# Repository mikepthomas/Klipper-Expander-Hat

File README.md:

# Klipper Fan Hat

[Interactive bom](https://klipper-fan-hat.mikethomas.info/)

### A Hat to use with the [Raspberry Pi as a Secondary MCU in Klipper](https://www.klipper3d.org/RPi_microcontroller.html):
- SKR Pico compatible input for powering the Pi and Serial communication
- 5 Mosfet outputs (with 2 pin JST-XH connectors standard on most fans used on 3D printers)
- Voltage selector jumpers to power each fan from either 5V or VCC supplied by screw terminal
- I2C and 1-Wire and SPI headers for connecting accesories to the Raspberry Pi
- 6 headers connected to General Purpose GPIO pins for accesories such as Filament Run Out Sensors
- On Board DS18B20 Temperature Sensor

### Documentation

[Documentation and Setup information here](Documentation/README.md)

 Parts that I sourced for assembly:
- 1206 Capacitor Set [Ali Express](https://www.aliexpress.com/item/1005002907508304.html)
- 1206 LEDs [Ali Express](https://www.aliexpress.com/item/1005003836509392.html)
- 1206 Resistor Set [Ali Express](https://www.aliexpress.com/item/33029877427.html)
- 2510 Axial Fan [Ali Express](https://www.aliexpress.com/item/32807610078.html)
- Blade Fuse Holder [Ali Express](https://www.aliexpress.com/item/1005003194700697.html)
- DIP-8 24C32 EEPROM [Ali Express](https://www.aliexpress.com/item/33036366759.html)
- DIP-8 Socket [Ali Express](https://www.aliexpress.com/item/1005001650813894.html)
- IRLML6344TRPBF Mosfets [Ali Express](https://www.aliexpress.com/item/1005004711783484.html)
- JST-XH Connector Set [Ali Express](https://www.aliexpress.com/item/33000442968.html)
- Jumper Caps [Ali Express](https://www.aliexpress.com/item/1005004482029258.html)
- KF301 Screw Terminal [Ali Express](https://www.aliexpress.com/item/1005003311688833.html)
- M2.5x14 BHCS [Ali Express](https://www.aliexpress.com/item/1005004123548619.html)
- Pin Header Set [Amazon](https://www.amazon.co.uk/gp/product/B07CWSXY7P)
- Raspberry Pi Headers and Spacers [Amazon](https://www.amazon.co.uk/gp/product/B07PHBTTGV)
- DS18B20 Temperature Sensor [Ali Express](https://www.aliexpress.com/item/1783091649.html)

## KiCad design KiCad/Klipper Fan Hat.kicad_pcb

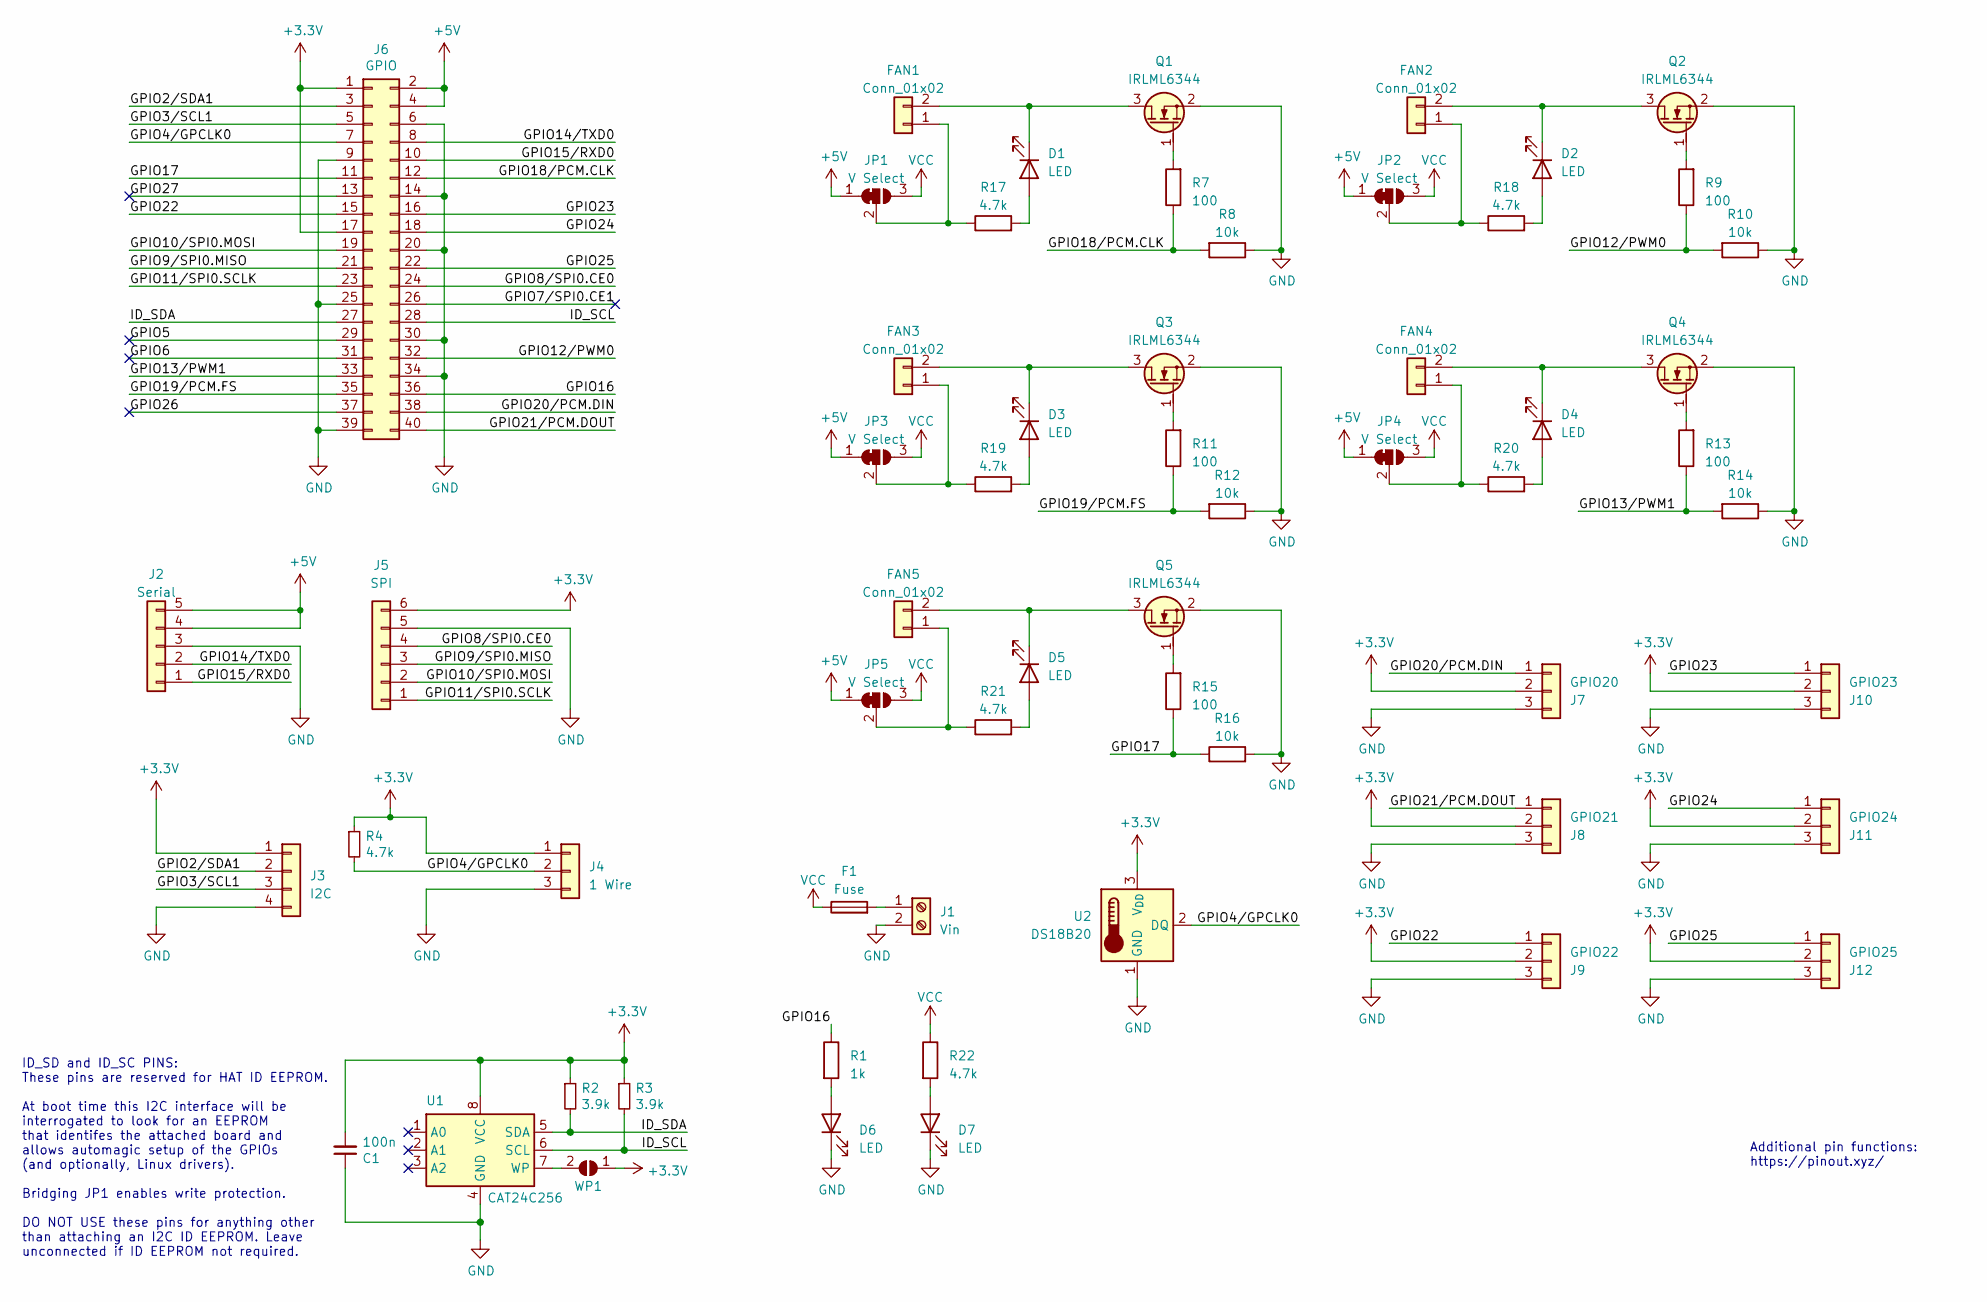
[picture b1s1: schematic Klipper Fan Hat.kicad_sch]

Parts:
C1: 100n; C_1206_3216Metric
D1, D2, D3, D4, D5, D6, D7: LED; LED_1206_3216Metric_ReverseMount_Hole1.8x2.4mm
F1: Fuse; Fuseholder_Blade_Mini_Keystone_3568
FAN1, FAN2, FAN3, FAN4, FAN5: Conn_01x02; JST_XH_B2B-XH-A_1x02_P2.50mm_Vertical
GPIO20: J7; PinHeader_1x03_P2.54mm_Vertical
GPIO21: J8; PinHeader_1x03_P2.54mm_Vertical
GPIO22: J9; PinHeader_1x03_P2.54mm_Vertical
GPIO23: J10; PinHeader_1x03_P2.54mm_Vertical
GPIO24: J11; PinHeader_1x03_P2.54mm_Vertical
GPIO25: J12; PinHeader_1x03_P2.54mm_Vertical
J1: Vin; TerminalBlock_bornier-2_P5.08mm
J2: Serial; JST_XH_B5B-XH-A_1x05_P2.50mm_Vertical
J3: I2C; JST_XH_B4B-XH-A_1x04_P2.50mm_Vertical
J4: 1 Wire; JST_XH_B3B-XH-A_1x03_P2.50mm_Vertical
J5: SPI; PinHeader_1x06_P2.54mm_Vertical
J6: GPIO; PinSocket_2x20_P2.54mm_Vertical
JP1, JP2, JP3, JP4, JP5: V Select; PinHeader_1x03_P2.54mm_Vertical
Q1, Q2, Q3, Q4, Q5: IRLML6344; TSOT-23
R1: 1k; R_1206_3216Metric
R2, R3: 3.9k; R_1206_3216Metric
R4, R17, R18, R19, R20, R21, R22: 4.7k; R_1206_3216Metric
R7, R9, R11, R13, R15: 100; R_1206_3216Metric
R8, R10, R12, R14, R16: 10k; R_1206_3216Metric
U1: CAT24C256; DIP-8_W7.62mm
U2: DS18B20; TO-92_Inline
WP1: ID_WP; PinHeader_1x02_P2.54mm_Vertical

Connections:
+3V3: C1.2, GPIO20.2, GPIO21.2, GPIO22.2, GPIO23.2, GPIO24.2, GPIO25.2, J3.1, J4.1, J5.6, J6.1, J6.17, R2.1, R3.1, R4.1, U1.8 (VCC), U2.3 (V_{DD}), WP1.1 (A)
+5V: J2.4, J2.5, J6.2, J6.4, JP1.1 (A), JP2.1 (A), JP3.1 (A), JP4.1 (A), JP5.1 (A)
/GPIO2/SDA1: J3.2, J6.3
/GPIO3/SCL1: J3.3, J6.5
/GPIO4/GPCLK0: J4.2, J6.7, R4.2, U2.2 (DQ)
/GPIO5: J6.29
/GPIO6: J6.31
/GPIO7/SPI0.CE1: J6.26
/GPIO8/SPI0.CE0: J5.4, J6.24
/GPIO9/SPI0.MISO: J5.3, J6.21
/GPIO10/SPI0.MOSI: J5.2, J6.19
/GPIO11/SPI0.SCLK: J5.1, J6.23
/GPIO12/PWM0: J6.32, R9.1, R10.2
/GPIO13/PWM1: J6.33, R13.1, R14.2
/GPIO14/TXD0: J2.2, J6.8
/GPIO15/RXD0: J2.1, J6.10
/GPIO16: J6.36, R1.1
/GPIO17: J6.11, R15.1, R16.1
/GPIO18/PCM.CLK: J6.12, R7.1, R8.2
/GPIO19/PCM.FS: J6.35, R11.1, R12.2
/GPIO20/PCM.DIN: GPIO20.1, J6.38
/GPIO21/PCM.DOUT: GPIO21.1, J6.40
/GPIO22: GPIO22.1, J6.15
/GPIO23: GPIO23.1, J6.16
/GPIO24: GPIO24.1, J6.18
/GPIO25: GPIO25.1, J6.22
/GPIO26: J6.37
/GPIO27: J6.13
/ID_SCL: J6.28, R3.2, U1.6 (SCL)
/ID_SDA: J6.27, R2.2, U1.5 (SDA)
GND: C1.1, D6.1 (K), D7.1 (K), GPIO20.3, GPIO21.3, GPIO22.3, GPIO23.3, GPIO24.3, GPIO25.3, J1.2, J2.3, J3.4, J4.3, J5.5, J6.6, J6.9, J6.14, J6.20, J6.25, J6.30, J6.34, J6.39, Q1.2 (S), Q2.2 (S), Q3.2 (S), Q4.2 (S), Q5.2 (S), R8.1, R10.1, R12.1, R14.1, R16.2, U1.4 (GND), U2.1 (GND)
unnamed: D1.2 (A), R17.2
unnamed: D1.1 (K), FAN1.2, Q1.3 (D)
unnamed: D2.2 (A), R18.2
unnamed: D2.1 (K), FAN2.2, Q2.3 (D)
unnamed: D3.2 (A), R19.2
unnamed: D3.1 (K), FAN3.2, Q3.3 (D)
unnamed: D4.2 (A), R20.2
unnamed: D4.1 (K), FAN4.2, Q4.3 (D)
unnamed: D5.2 (A), R21.2
unnamed: D5.1 (K), FAN5.2, Q5.3 (D)
unnamed: D6.2 (A), R1.2
unnamed: D7.2 (A), R22.2
unnamed: FAN1.1, JP1.2 (C), R17.1
unnamed: FAN2.1, JP2.2 (C), R18.1
unnamed: FAN3.1, JP3.2 (C), R19.1
unnamed: FAN4.1, JP4.2 (C), R20.1
unnamed: FAN5.1, JP5.2 (C), R21.1
unnamed: F1.2, J1.1
unnamed: Q1.1 (G), R7.2
unnamed: Q2.1 (G), R9.2
unnamed: Q3.1 (G), R11.2
unnamed: Q4.1 (G), R13.2
unnamed: Q5.1 (G), R15.2
unnamed: U1.7 (WP), WP1.2 (B)
VCC: F1.1, JP1.3 (B), JP2.3 (B), JP3.3 (B), JP4.3 (B), JP5.3 (B), R22.1

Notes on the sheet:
Additional pin functions: https://pinout.xyz/
ID_SD and ID_SC PINS: These pins are reserved for HAT ID EEPROM. At boot time this I2C interface will be interrogated to look for an EEPROM that identifes the attached board and allows automagic setup of the GPIOs (and optionally, Linux drivers). Bridging JP1 enables write protection. DO NOT USE th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

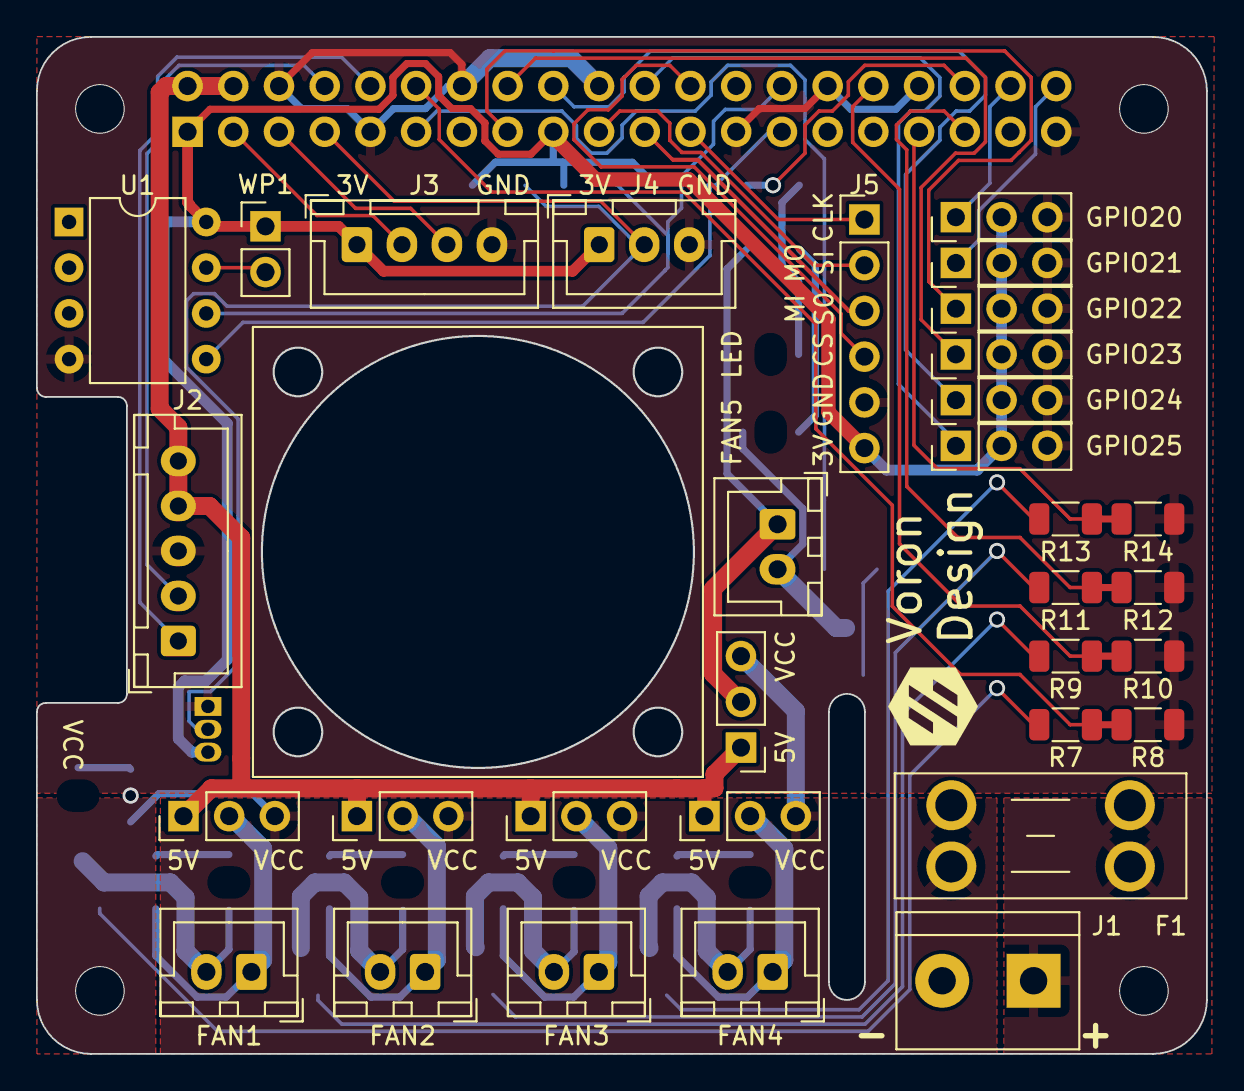
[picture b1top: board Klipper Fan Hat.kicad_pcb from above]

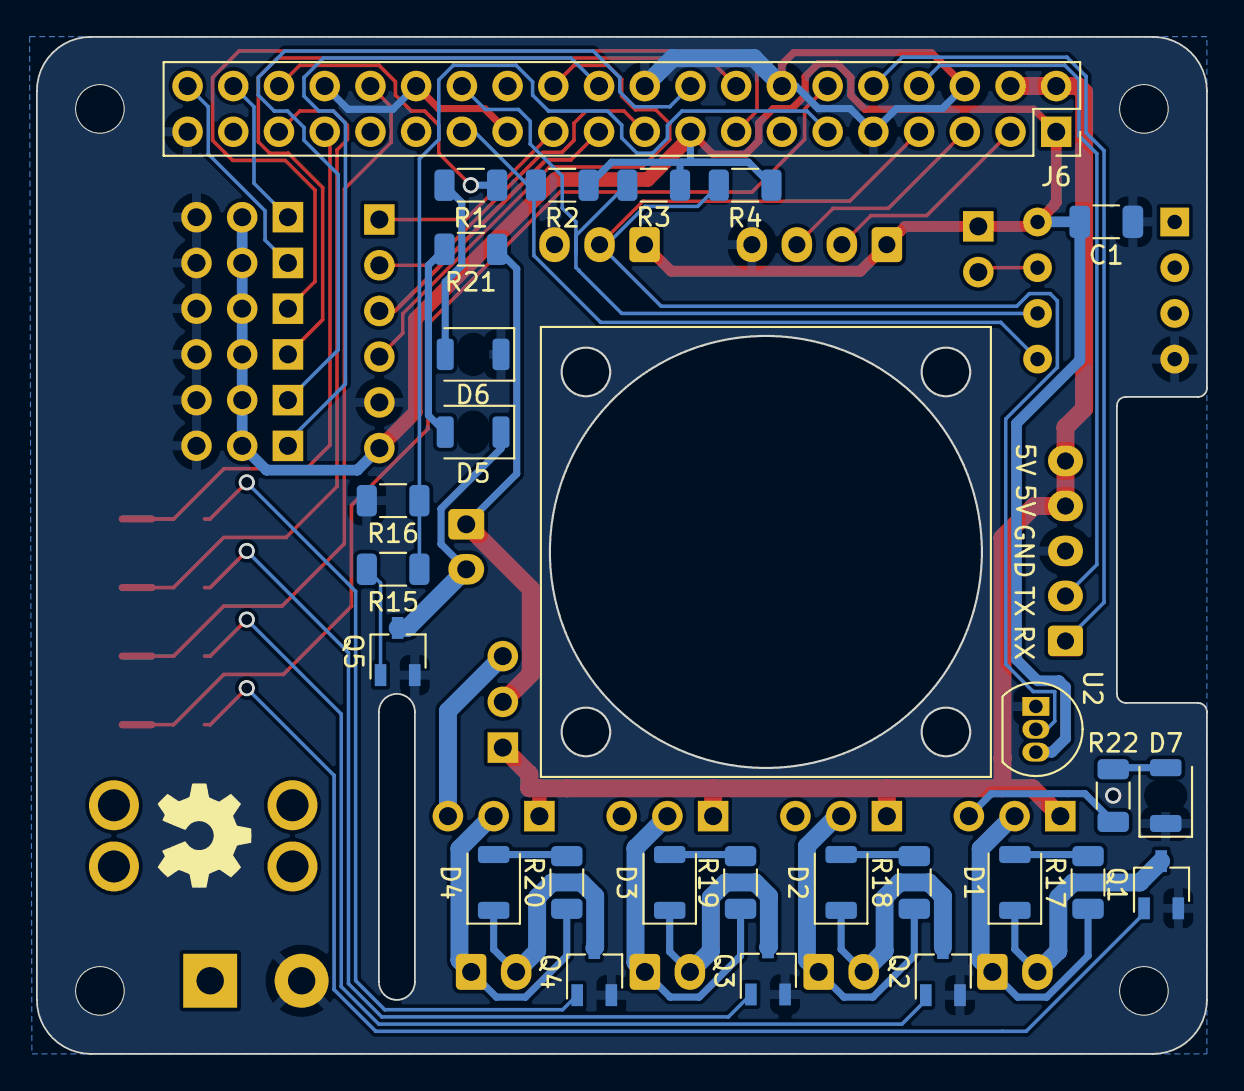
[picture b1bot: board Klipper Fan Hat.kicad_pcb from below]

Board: 2 copper layers, 65.0 x 56.5 mm, 63 parts (27 on the bottom side), 51 nets.

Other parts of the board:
MH1, MH2, MH3, MH4: MountingHole_2.7mm_M2.5

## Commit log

2023-07-21 update values of pull up resistors
2023-08-09 Update KlippUpdate Klipper Fan Hat to expose more GPIO pins and add an on board DS18B20 Temperature Sensor
2023-08-09 Update Interactive BOM
2023-08-09 Update Serial Header Ground connection
2023-08-09 Add correct Gerber files
2023-12-08 Create CNAME
2023-12-08 Update link to interactive BOM

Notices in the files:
KiCad/Klipper Fan Hat.kicad_pcb:
GNU General Public License v3.0
